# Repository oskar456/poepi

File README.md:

PoEpi: a multi purpose shield for Raspberry Pi
==============================================

This is a peripheral board for [Raspberry Pi](http://www.raspberrypi.org) with
three separate functions:

* Power supply with 12-40&nbsp;Volt input and 5&nbsp;Volt, 0.75&nbsp;Amps output,
with short circuit protection and simple passive PoE extractor (utilizes unused
pairs in a Fast Ethernet UTP cable).
* [1-Wire](http://en.wikipedia.org/wiki/1-Wire) controller
[DS2482-100](http://www.maximintegrated.com/datasheet/index.mvp/id/4382)
connected to I2C bus of Raspberry Pi.
* Real time clock module
[PCF8583](http://www.nxp.com/products/interface_and_connectivity/i2c/rtcs_with_i2c_interface/series/PCF8583.html)
with backup battery.

All schematics and board layouts are created using [EAGLE 6.2.1 beta](http://www.cadsoftusa.com).

For more informations, please visit [PoEpi pages](http://oskar456.github.io/poepi/).

List of schematics and boards
-----------------------------

* **PoEpi_v2**: current board design
* **PoEpi_proto**: old prototype board design
* **PoE_injector**: simple injector, utilizing unused pairs in a Fast Ethernet UTP cable.

### Copyright

Copyright 2013 Ondřej Caletka  
This work is licensed under a [Creative Commons Attribution 3.0 Unported License][lic].  
[![Creative Commons License][licimg]][lic]

[lic]: http://creativecommons.org/licenses/by/3.0/
[licimg]: http://i.creativecommons.org/l/by/3.0/88x31.png

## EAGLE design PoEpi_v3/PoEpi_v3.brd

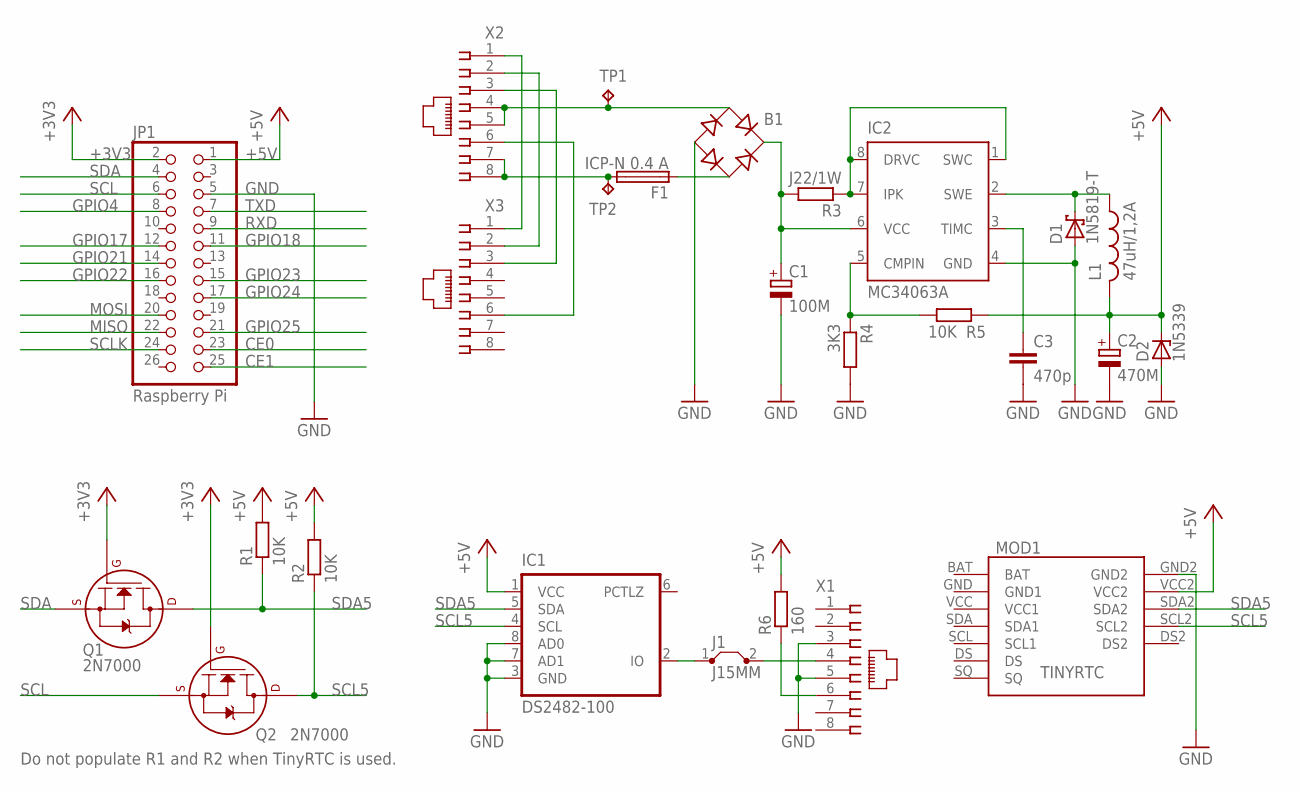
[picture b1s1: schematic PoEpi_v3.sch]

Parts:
B1: B-DIL
C1: 100M; E3,5-8
C2: 470M; E3,5-8
C3: 470p; C050-024X044
D1: 1N5819-T; DO41-7.6
D2: 1N5339; C1702-15
F1: ICP-N 0.4 A; TO92-2
IC1: DS2482-100; SO08
IC2: MC34063A; DIL8
J1: J15MM; 15
JP1: Raspberry Pi; 2X13
L1: 47uH/1,2A; 6000-XXXX-RC
MOD1: TINYRTC; TINYRTCMODULE
Q1, Q2: 2N7000; TO92-
R1, R2, R5: 10K; 0204/7
R3: J22/1W; 0617/17
R4: 3K3; 0204/7
R6: 160; 0204/7
TP1, TP2: TPPAD1-13Y; P1-13Y
X1, X2, X3: 520251-4

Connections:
+3V3: JP1.2 (1), Q1.2 (G), Q2.2 (G)
+5V: C2.+, D2.C, IC1.1 (VCC), JP1.1 (2), L1.2, MOD1.VCC2, R1.2, R2.2, R5.2, R6.2
BAT: MOD1.BAT
CE0: JP1.23 (24)
CE1: JP1.25 (26)
GND: B1.-, C1.-, C2.-, C3.2, D1.A, D2.A, IC1.3 (GND), IC1.7 (AD1), IC1.8 (AD0), IC2.4 (GND), JP1.5 (6), MOD1.GND2, R4.2, X1.3, X1.5
GND1: MOD1.GND (GND1)
GPIO4: JP1.8 (7)
GPIO17: JP1.12 (11)
GPIO18: JP1.11 (12)
GPIO21: JP1.14 (13)
GPIO22: JP1.16 (15)
GPIO23: JP1.15 (16)
GPIO24: JP1.17 (18)
GPIO25: JP1.21 (22)
MISO: JP1.22 (21)
MOSI: JP1.20 (19)
unnamed: X2.1, X3.1
unnamed: X2.2, X3.2
unnamed: X2.3, X3.3
unnamed: X2.6, X3.6
unnamed: F1.3 (2), TP2.TP, X2.7, X2.8
unnamed: B1.AC1, TP1.TP, X2.4, X2.5
unnamed: IC2.1 (SWC), IC2.7 (IPK), IC2.8 (DRVC), R3.1
unnamed: IC2.5 (CMPIN), R4.1, R5.1
unnamed: B1.+, C1.+, IC2.6 (VCC), R3.2
unnamed: C3.1, IC2.3 (TIMC)
unnamed: R6.1, X1.6
unnamed: D1.C, IC2.2 (SWE), L1.1
unnamed: B1.AC2, F1.1
ONEWIRE: IC1.2 (IO), J1.1
ONEWIRE2: J1.2, X1.4
RXD: JP1.9 (10)
SCL: JP1.6 (5), Q2.3 (S)
SCL5: IC1.4 (SCL), MOD1.SCL2, Q2.1 (D), R2.1
SCLK: JP1.24 (23)
SDA: JP1.4 (3), Q1.3 (S)
SDA5: IC1.5 (SDA), MOD1.SDA2, Q1.1 (D), R1.1
TXD: JP1.7 (8)
VCC1: MOD1.VCC (VCC1)

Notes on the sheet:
Do not populate R1 and R2 when TinyRTC is used.

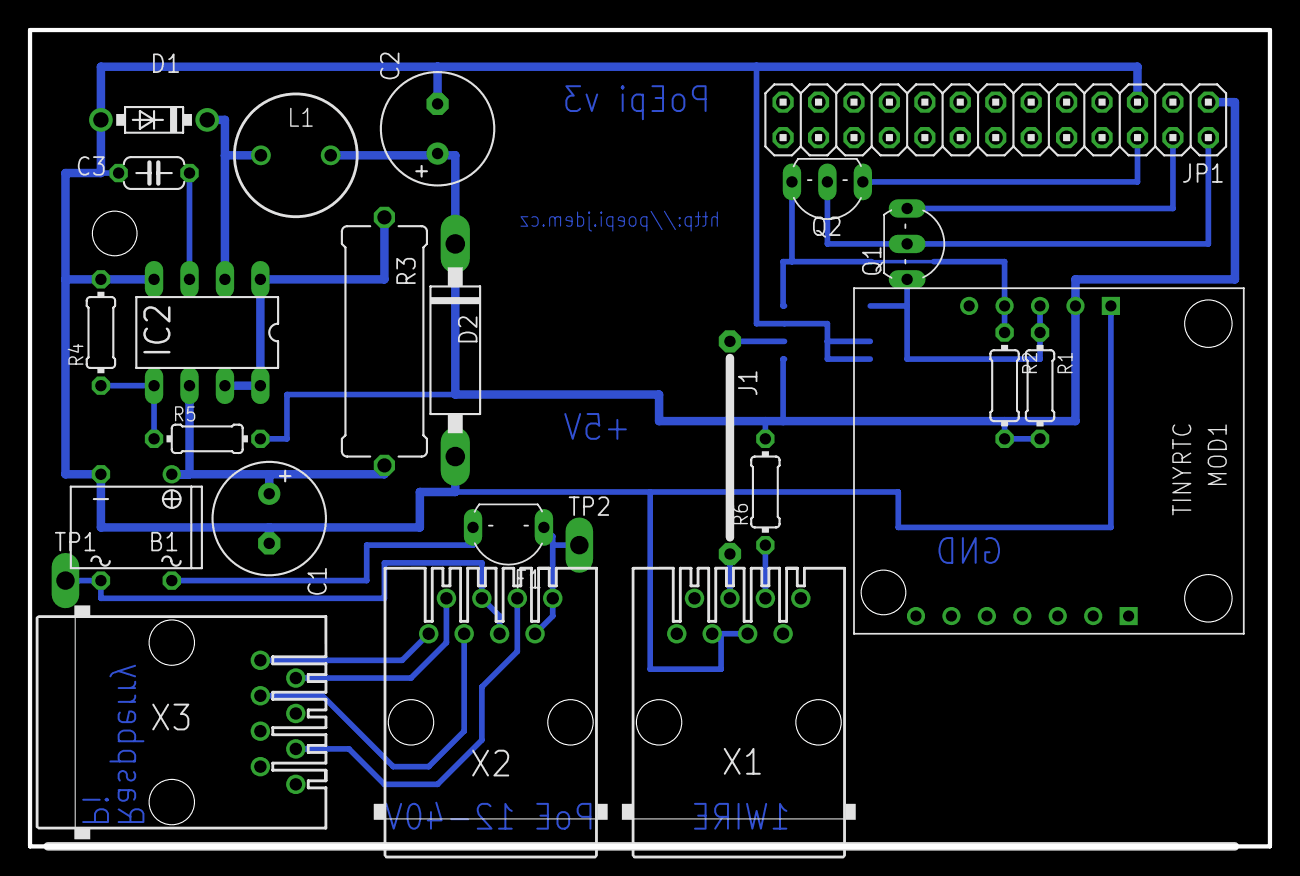
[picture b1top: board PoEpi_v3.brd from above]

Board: 2 copper layers, 88.9 x 58.5 mm, 26 parts (1 on the bottom side), 22 nets.

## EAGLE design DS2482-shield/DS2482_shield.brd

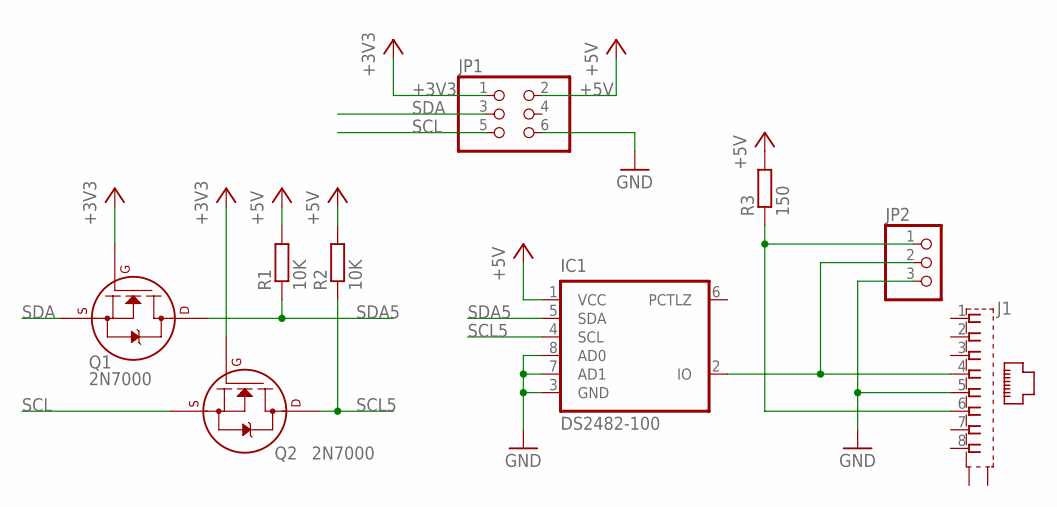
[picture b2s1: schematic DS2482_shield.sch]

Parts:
IC1: DS2482-100; SO08
J1: 555153-1
JP1: PINHD-2X3; 2X03
JP2: PINHD-1X3; 1X03
Q1, Q2: 2N7000; TO92-
R1, R2: 10K; 0204/7
R3: 150; 0204/7

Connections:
+3V3: JP1.1, Q1.2 (G), Q2.2 (G)
+5V: IC1.1 (VCC), JP1.2, R1.2, R2.2, R3.2
GND: IC1.3 (GND), IC1.7 (AD1), IC1.8 (AD0), J1.5, JP1.6, JP2.3
unnamed: J1.6, JP2.1, R3.1
ONEWIRE: IC1.2 (IO), J1.4, JP2.2
SCL: JP1.5, Q2.3 (S)
SCL5: IC1.4 (SCL), Q2.1 (D), R2.1
SDA: JP1.3, Q1.3 (S)
SDA5: IC1.5 (SDA), Q1.1 (D), R1.1

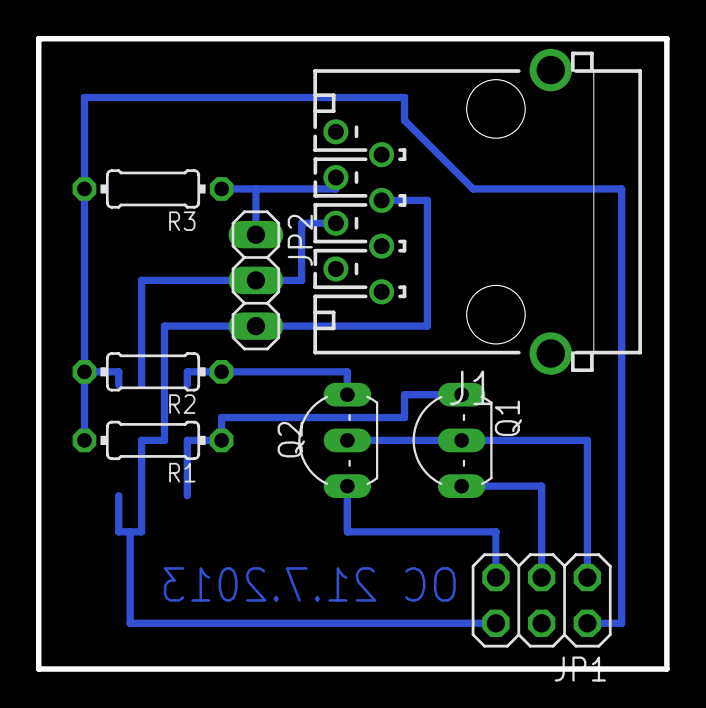
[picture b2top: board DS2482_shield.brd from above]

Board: 2 copper layers, 34.9 x 35.0 mm, 9 parts (1 on the bottom side), 9 nets.

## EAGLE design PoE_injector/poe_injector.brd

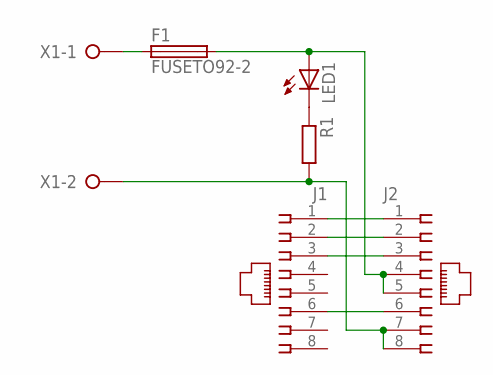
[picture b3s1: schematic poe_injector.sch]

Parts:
F1: FUSETO92-2; TO92-2
J1, J2: 520251-4
LED1: LED3MM
R1: R-EU_0207/10; 0207/10
X1: W237-02P; W237-132

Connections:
GND-7,8: J2.7, J2.8, R1.2, X1.2
unnamed: J1.1, J2.1
unnamed: J1.2, J2.2
unnamed: J1.3, J2.3
unnamed: J1.6, J2.6
unnamed: LED1.K (C), R1.1
unnamed: F1.1, X1.1
VCC-5,6: F1.3 (2), J2.4, J2.5, LED1.A

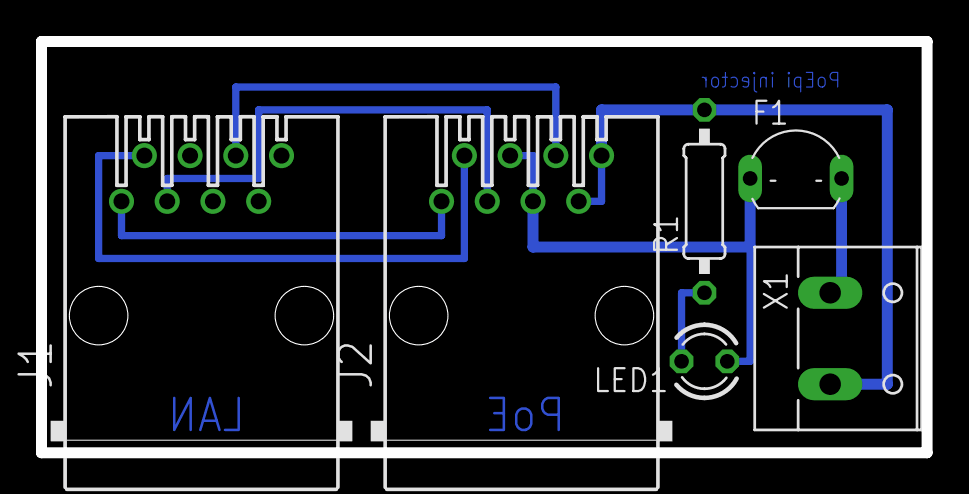
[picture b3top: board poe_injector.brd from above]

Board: 2 copper layers, 49.2 x 22.9 mm, 6 parts (0 on the bottom side), 8 nets.

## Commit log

2013-04-26 Import project files
2013-04-26 Added a README
2013-04-26 Create gh-pages branch via GitHub
2013-04-26 Added schematics
2013-04-26 Added protoboard photo
2013-04-26 Transparent schematics
2013-04-26 Schematics cleanup
2013-04-26 PoE injector cleanup, added png and PDF
2013-04-26 Readme update.
2013-04-26 Added injector schematics
2013-04-26 PoEpi-injector.png with transparent background
2013-07-21 Simple shield for DS2482
2014-01-19 Add version 3
    This version uses TinyRTC module for Arduino for RTC
    TinyRTC is much more cheaper than RTC from discrete components
    (http://jdem.cz/9jme9) but precission is not very good.
